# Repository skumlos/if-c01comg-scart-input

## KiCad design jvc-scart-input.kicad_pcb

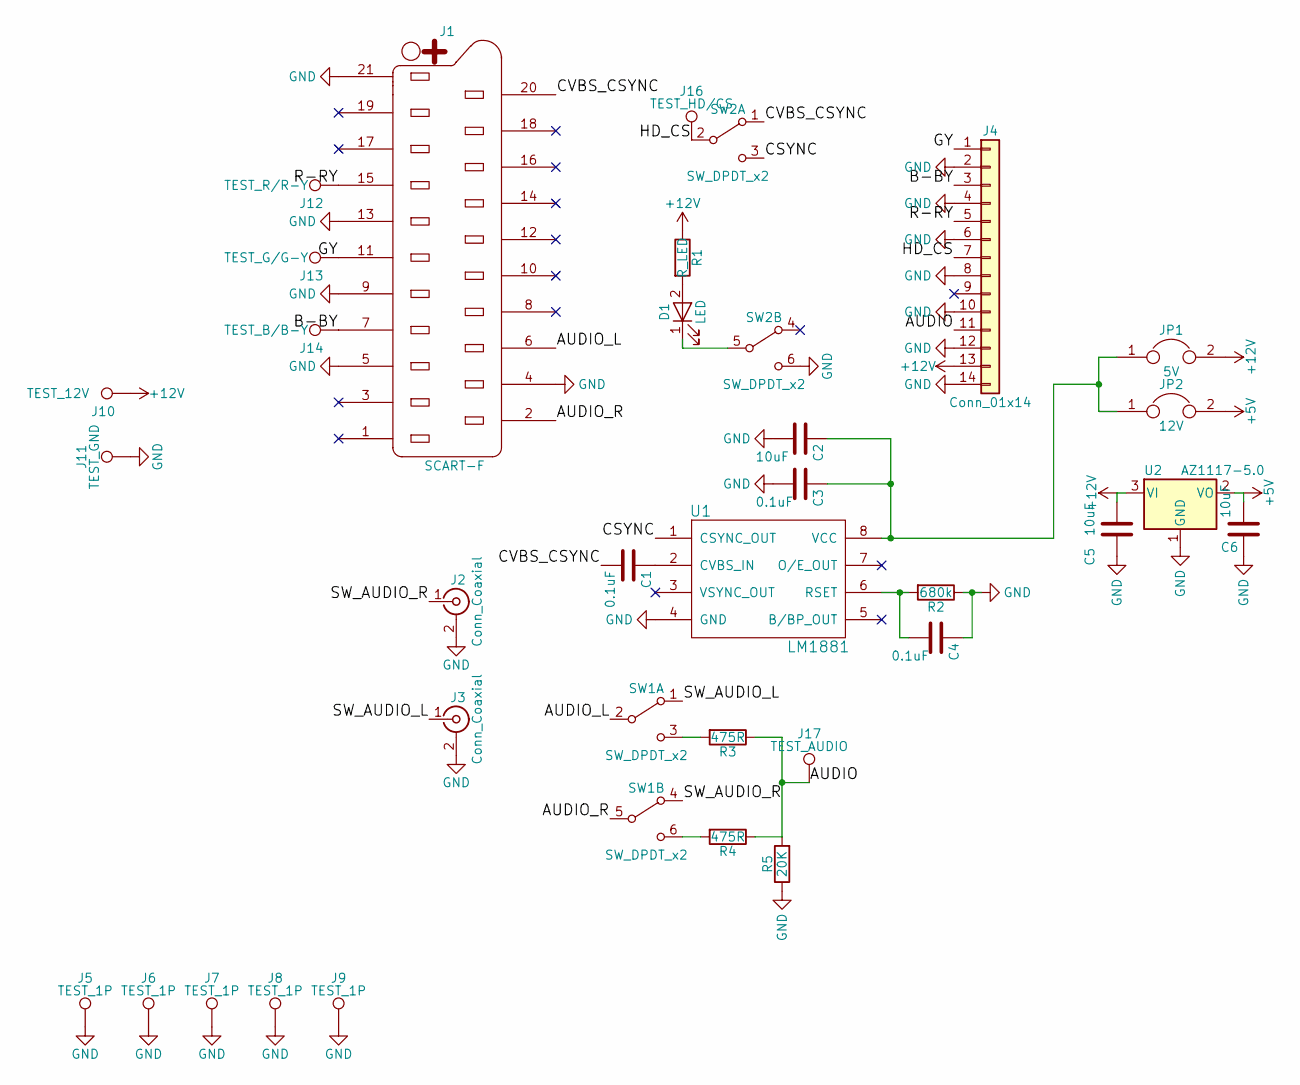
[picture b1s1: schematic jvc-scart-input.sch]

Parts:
C1, C3, C4: 0.1uF; C_0805_HandSoldering
C2, C5, C6: 10uF; C_0805_HandSoldering
D1: LED; LED_D5.0mm
J1: SCART-F; K-SCARTX-024
J2, J3: Conn_Coaxial; RCJ-02
J4: Conn_01x14; 52852-1472
J5, J6, J7, J8, J9: TEST_1P; MountingHole_3.2mm_M3
J10: TEST_12V; Measurement_Point_Round-SMD-Pad_Small
J11: TEST_GND; Measurement_Point_Round-SMD-Pad_Small
J12: TEST_R/R-Y; Measurement_Point_Round-SMD-Pad_Small
J13: TEST_G/G-Y; Measurement_Point_Round-SMD-Pad_Small
J14: TEST_B/B-Y; Measurement_Point_Round-SMD-Pad_Small
J16: TEST_HD/CS; Measurement_Point_Round-SMD-Pad_Small
J17: TEST_AUDIO; Measurement_Point_Round-SMD-Pad_Small
JP1: 5V; SMD-JUMPER
JP2: 12V; SMD-JUMPER
R1: R_LED; R_0805_HandSoldering
R2: 680k; R_0805_HandSoldering
R3, R4: 475R; R_0805_HandSoldering
R5: 20K; R_0805_HandSoldering
SW1, SW2: SW_DPDT_x2; eswitch-dpdt-m2
U1: LM1881; SOIC-8_3.9x4.9mm_Pitch1.27mm
U2: AZ1117-5.0; SOT-223

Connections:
+5V: C6.2, JP2.2, U2.2 (VO)
+12V: C5.2, J4.13, J10.1, JP1.2, R1.1, U2.3 (VI)
/AUDIO: J4.11, J17.1, R3.1, R4.1, R5.2
/AUDIO_L: J1.6, SW1.2 (B)
/AUDIO_R: J1.2, SW1.5 (B)
/B-BY: J1.7, J4.3, J14.1
/CSYNC: SW2.3 (C), U1.1 (CSYNC_OUT)
/CVBS_CSYNC: C1.2, J1.20, SW2.1 (A)
/GY: J1.11, J4.1, J13.1
/HD_CS: J4.7, J16.1, SW2.2 (B)
/R-RY: J1.15, J4.5, J12.1
/SW_AUDIO_L: J3.1 (In), SW1.1 (A)
/SW_AUDIO_R: J2.1 (In), SW1.4 (A)
GND: C2.2, C3.2, C4.1, C5.1, C6.1, J1.4, J1.5, J1.9, J1.13, J1.21, J2.2 (Ext), J3.2 (Ext), J4.2, J4.4, J4.6, J4.8, J4.10, J4.12, J4.14, J5.1, J6.1, J7.1, J8.1, J9.1, J11.1, R2.1, R5.1, SW2.6 (C), U1.4 (GND), U2.1 (GND)
unnamed: C1.1, U1.2 (CVBS_IN)
unnamed: C2.1, C3.1, JP1.1, JP2.1, U1.8 (VCC)
unnamed: C4.2, R2.2, U1.6 (RSET)
unnamed: D1.1 (K), SW2.5 (B)
unnamed: D1.2 (A), R1.2
unnamed: R3.2, SW1.3 (C)
unnamed: R4.2, SW1.6 (C)

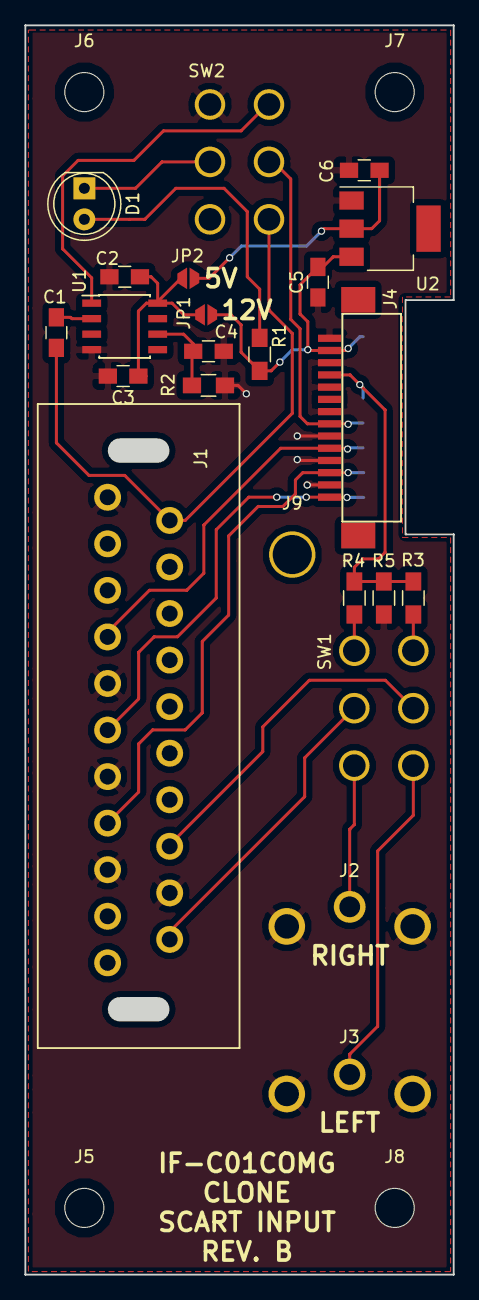
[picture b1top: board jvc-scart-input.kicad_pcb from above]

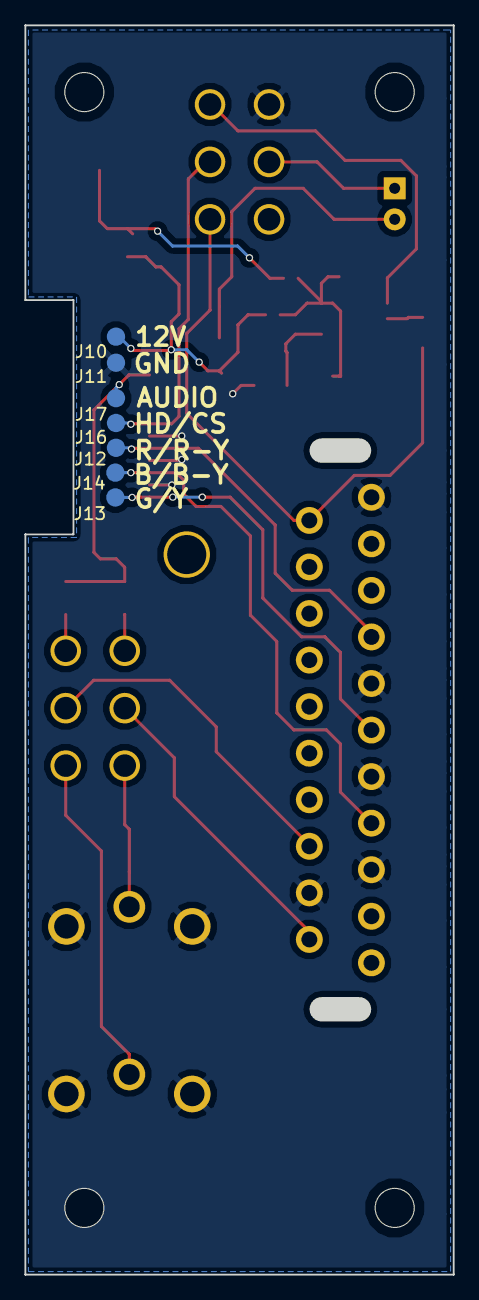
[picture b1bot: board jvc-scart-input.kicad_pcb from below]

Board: 2 copper layers, 35.1 x 102.2 mm, 34 parts (7 on the bottom side), 21 nets.
